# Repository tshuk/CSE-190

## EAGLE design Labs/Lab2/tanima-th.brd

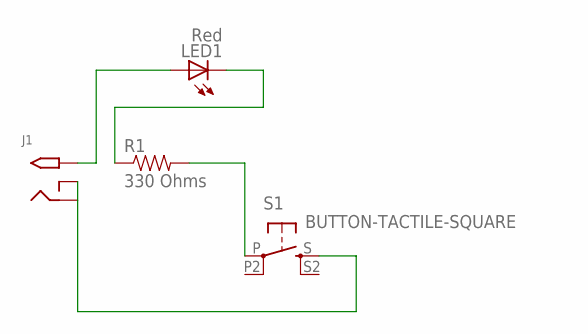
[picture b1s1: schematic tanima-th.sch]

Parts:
J1: 2.1MMJACKTHM; PJ-102A
LED1: Red; LED5MM
R1: 330 Ohms; AXIAL-0.3
S1: BUTTON-TACTILE-SQUARE; BUTTON-TACTILE-SQUARE-ADAFRUIT1010

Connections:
unnamed: R1.P$2 (2), S1.P
unnamed: LED1.K (C), R1.P$1 (1)
unnamed: J1.TIP, LED1.A
unnamed: J1.RING, J1.RING_SW, S1.S

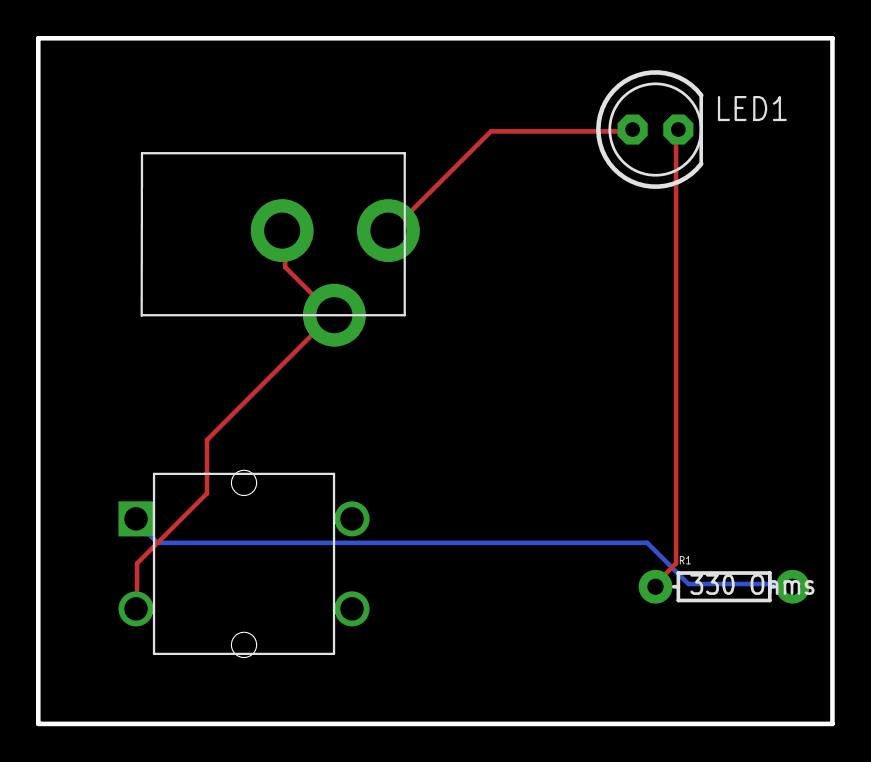
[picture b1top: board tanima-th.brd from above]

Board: 2 copper layers, 44.1 x 38.1 mm, 4 parts (0 on the bottom side), 4 nets.

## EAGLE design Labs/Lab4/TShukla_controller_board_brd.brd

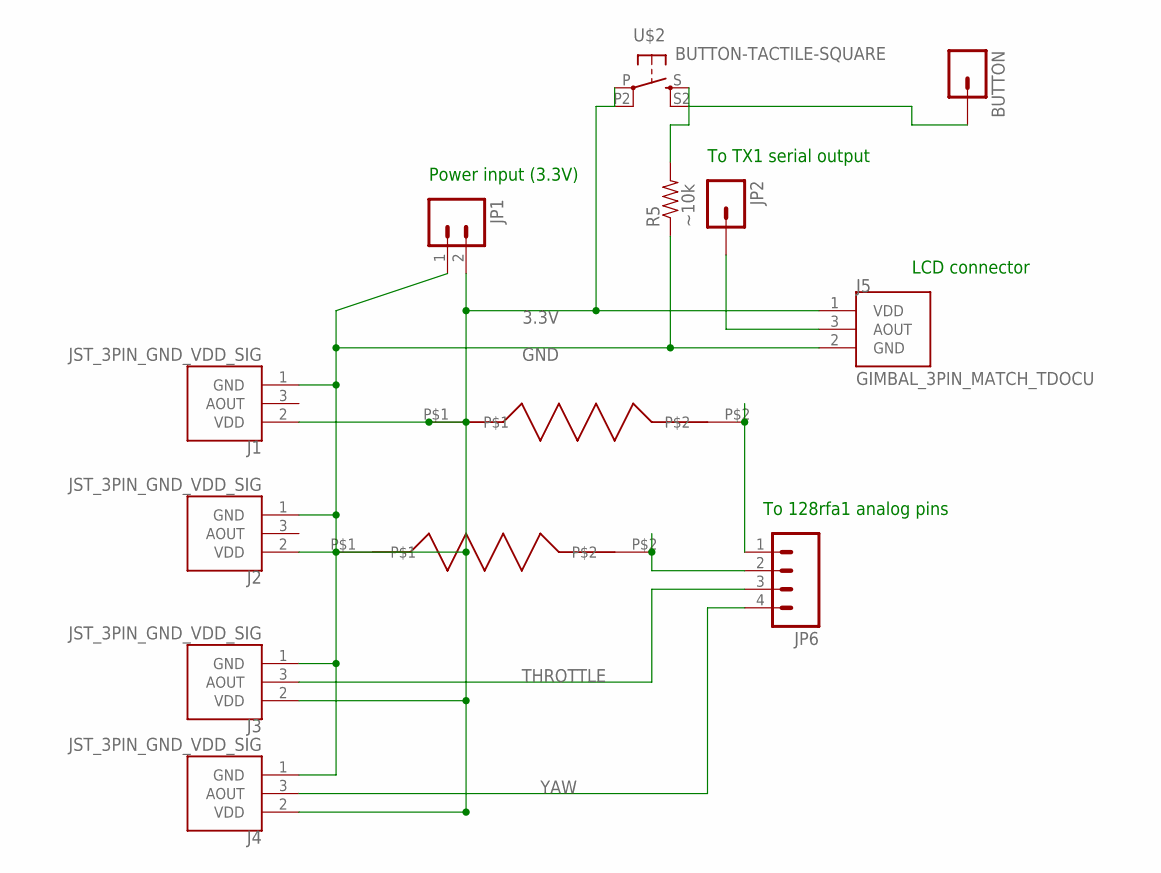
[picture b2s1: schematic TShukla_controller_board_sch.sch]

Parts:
BUTTON: M01PTH; 1X01
J1, J2, J3, J4: JST_3PIN_GND_VDD_SIG; JST-3-PTH-REVERSE
J5: GIMBAL_3PIN_MATCH_TDOCU; JST-3-PTH
JP1: M021X02_NO_SILK; 1X02_NO_SILK
JP2: M01PTH; 1X01
JP6: M04PTH; 1X04
R5: ~10k; AXIAL-0.4
U$2: BUTTON-TACTILE-SQUARE; BUTTON-TACTILE-SQUARE-ADAFRUIT1010
U$3, U$4: THROUGH_HOLE_RESISTOR; DIODE(SMB)

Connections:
3.3V: J1.2 (VDD), J2.2 (VDD), J3.2 (VDD), J4.2 (VDD), J5.1 (VDD), JP1.2, U$2.P, U$2.P2 (P1), U$3.P$1, U$4.P$1
GND: J1.1 (GND), J2.1 (GND), J3.1 (GND), J4.1 (GND), J5.2 (GND), JP1.1, R5.P$1 (1)
unnamed: BUTTON.1, R5.P$2 (2), U$2.S, U$2.S2 (S1)
unnamed: J5.3 (AOUT), JP2.1
PITCH: JP6.1, U$4.P$2
ROLL: JP6.2, U$3.P$2
THROTTLE: J3.3 (AOUT), JP6.3
YAW: J4.3 (AOUT), JP6.4

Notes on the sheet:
To 128rfa1 analog pins
LCD connector
Power input (3.3V)
To TX1 serial output

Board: 2 copper layers, 14 parts (1 on the bottom side), 8 nets, no tracks yet.

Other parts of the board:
U$1: CONNECTOR_BOARD_OUTLINE

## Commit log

2015-04-02 initial RadioTest.ino commit
2015-04-02 RadioTest: message timestamps and packet counting
2015-04-02 added rfWriteFrame and frame test
2015-04-08 create LabReports directory and add code
2015-04-08 add Lab1Report.pdf in turnin directory
2015-04-10 Schematic board, cam files, and new new library
    Files of the schematic and board with the cam files. and the new made
    button.
    As of now, I am having a lot of trouble adding the button to the
    schematic. The button appears in the library in the board file, but not
    in the schematic. I will try to figure this out in the next.
2015-04-17 Lab 4 Files
    My library, controller schematic and board, and CAM files

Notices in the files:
parts and their libraries:
SparkFun-Connectors: Licensing: Creative Commons ShareAlike 4.0 International - https://creativecommons.org/licenses/by-sa/4.0
